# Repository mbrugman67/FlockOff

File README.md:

# FlockOff
This project started as a device specifically to detect Flock security ALPR devices, but has grown into a more generic WiFi/Bluetooth LE scanner/alert wardriving tool.

## Description
This started of strictly as a Flock detector, but grew into more.  In general, it is a device to monitor WiFi and BTLE networks, setting an indicator whenever a broadcaster is found that meets preset parameters.  For WiFi networks, those parameters can be a MAC OID or network name (SSID).  For Bluetooth, the matching criteria can be name, MAC, or by specific 16-bit UUIDs.

The hardware device consists of an ESP32-S3 dev board, a serial GPS module, and two LEDs for alerts and status.

There is a serial interface to the hardware device with a rich CLI (command-line interface).  The device can also be used stand-alone (results are stored to internal file system) or by scripting.

## Project structure
The files contained in the project:
+ `./hardware` - contains a KiCad project for the board
+ `./img` - images used in this README
+ `./py` - simply python3 script to interact with the flocker (notes below)
+ `./src` - source code (arduino project) for the ESP32 (notes below)
+ `./case` - sample 3D printer `.stl` and openSCAD files for a case

### Hardware

The hardware is dead simple - two dev modules, two through-hole 8mm WS2812 LEDs, and a small signal diode:
+ [ESP32-S3](https://www.amazon.com/Dual-core-Supported-Efficiency-Interface-Robotics/dp/B0DJ6NQFKX/ref=sxin_17_pa_sp_search_thematic_sspa?content-id=amzn1.sym.acab9f82-fc77-4a20-9021-7b5c22d80ec5%3Aamzn1.sym.acab9f82-fc77-4a20-9021-7b5c22d80ec5&crid=2JDD3FE6II334&cv_ct_cx=esp32s3&keywords=esp32s3&pd_rd_i=B0DJ6NQFKX&pd_rd_r=111273b0-33b8-492d-943f-a421e25d3cd0&pd_rd_w=tgPcF&pd_rd_wg=AKjP3&pf_rd_p=acab9f82-fc77-4a20-9021-7b5c22d80ec5&pf_rd_r=M8JMDJXXJ54DR9BMEQC6&qid=1765833241&s=electronics&sbo=RZvfv%2F%2FHxDF%2BO5021pAnSA%3D%3D&sprefix=esp32s3%2Celectronics%2C142&sr=1-2-6024b2a3-78e4-4fed-8fed-e1613be3bcce-spons&aref=L2fTwRUg09&sp_csd=d2lkZ2V0TmFtZT1zcF9zZWFyY2hfdGhlbWF0aWM&th=1) I picked this module because of small size, good price, and 8MB of both flash and PSRAM
+ [GPS Module](https://www.amazon.com/hiBCTR-Navigation-Positioning-Microcontroller-Sensitivity/dp/B0FL71WTQY/ref=sr_1_2?crid=2EM3EOXRCSTFT&dib=eyJ2IjoiMSJ9.XRWR-WnPLsz7cVN0GpjqJTxFRMO10MBskzPEVvz5LCTDXAtxa_rXf2wQrFndRzU50l7y__POWiiDMUXVK5OIa7VqEst8IqFH4xFvcnBHg-U0VY4qNZQPKFdzWL5Evdyj4AFWD0VpzcrnOxwnca7-Dr8wspdKucj2aYc0Gtoa1uRUl7K4ES9h20ztgmGDT3mPrt2tiQ-HN-FAgOPFQVPE3Pudl5vF2LNCPSp00W8Bhg5xvlYpIlCSGdX8GwmWiVH8u0OJW8YW5ridkpLchugFbq4H7w5SYdWBFkT73FZqAvk.YyvKMYAZdg815_BV_j8Fv4HH-0O0dOLUrndqKjRR0CQ&dib_tag=se&keywords=4+Pack+GPS+Module%2C+NEO-6M+Navigation+Positioning%2C+Arduino+GPS+for+Drone+Microcontroller%2C+High+Sensitivity+Receiver+with+Antenna%2C+Compatible+with+51+Microcontroller+STM32+Arduino+UNO+R3&nsdOptOutParam=true&qid=1765833097&s=electronics&sprefix=4+pack+gps+module%2C+neo-6m+navigation+positioning%2C+arduino+gps+for+drone+microcontroller%2C+high+sensitivity+receiver+with+antenna%2C+compatible+with+51+microcontroller+stm32+arduino+uno+r3%2Celectronics%2C158&sr=1-2) There is nothing special about this particular module; it is a basic GPS with NMEA serial interface, it was cheap, and in stock at Amazon
+ [WS1812 LEDs](https://www.adafruit.com/product/1734)  These are interesting in that they are the typical addressable LEDs, but in a through-hole 8mm package.  They are great for using as status indicators.  Also handy because there are so many libraries to work with them.
+ [1N4148 Diode](amazon.com/ALLECIN-1N4148-Schottky-Switching-Package/dp/B0CKRMK45V/ref=sr_1_6_sspa?dib=eyJ2IjoiMSJ9.5f18Rx_7lMSBN-40Nk5_scirzd5gVqG_sr48GsP-pxJ7RyARr5GHbm76WgpJle4ywCwcEGfv6m5ZR-PIBoBmRN28qtEe29DQYY84c263_q6oFDujaGGVK8-qabhrRd_IZtu2PwFHkKMBdiIw8IDQjSYkBxPm9DKi_AA6exCA7rmOiWGNdN9Oq0D-5c1H1XGK1kBii_ftCc-F3YiORaBovQ5vkFW9kAN3zzAu7IgDKEk.RF6rc4KmtAVvY9uUuLV-Zf6xt-HBLaOGQf1vvRW5V2U&dib_tag=se&keywords=1n4148&qid=1765833550&sr=8-6-spons&sp_csd=d2lkZ2V0TmFtZT1zcF9tdGY&psc=1) (Amazon link for reference, I had some in my parts bin).  This is used because it has a forward voltage drop of about .7V.

#### What's up with the diode?

Like pretty much all WS2812 LEDs, these need 5VDC to operate; 5VDC power, 5VDC data line.  The ESP32 is a 3.3 microcontroller, so what to do?

The USB connection supplies 5V which is regulated down to 3.3V for the microcontroller and associated stuff.  In the schematic above, `D3` is shown between the 5V USB power and the LED power in pin; that drops the voltage to about 4.3VDC.  That's just within spec for the LED, and it is still plenty bright.

The 3.3V signal data line from the ESP32 would be too low if the LED was powered by 5V, but is within spec for the LED when it is running at 4.3-ish volts.  It's a cheat to get away without having to use level converters; not something I'd do for a "real" production project, but good enough for here.

### Firmware
The firmware is written using the Arduino IDE.  In the past, I've always avoided that and used VS Code with my own Makefile or CMAKE, PlatformIO, or whatever.  I decided to go with Arduino in this case because I'm very unhappy with the integration of Copilot into VS Code (and really, the push to shove AI into everything).  For now, Ardiuno is just code.

For more specific information, see the `DEVELOPING.md` file.

### CLI Interface
There is a CLI available at the USB port at 115200/8N1.  The CLI uses ANSII escape codes for color, has tab-completion, up-arrow recall, and help:
```  
Flock Off $>help 
Use 'command -h' for detailed help on each command
        help - Print list of commands
        version - Display firmware version
        survey - Perform WiFi survey
        scan - Start continuous scan
        clear - Clear the console
        reset - Reboot the device
        ls - List files
        rm - Delete file
        write - Write test file
        mv - Rename file
        cp - Copy file
        cat - Cat file
        status - Get system status
        config - Get/Set config values
        criteria - Get/Set target matching criteria
```  
Passing a `-h` to any command will show help for that command, for example:
```  
Flock Off $>survey -h
survey [OPTION]
Perform a WiFi and/or Bluetooth survey.  Displays all results, not just those that match scan criteria.

  -i <INTERVAL>   interval in milliseconds to scan each WiFi channel
  -f <FILENAME>   save results to FILENAME in JSON format
  -n <NOTES>      add NOTES added for reference

If the -f parameter is not passed, JSON results will be displayed in the terminal.
```  
There is a flat filesystem included (flat, meaning no directories; all files are in a single directory). Basic Linux-type file management commands are available, but note that there is no 'globbing'; all filenames must be directly entered.  Examples:
```  
      371  01/22/26  18:25:46  autoscan.1.log
      163  01/22/26  18:42:01  autoscan.log
      208  12/31/69  18:02:32  config.json
    11300  01/22/26  18:26:04  system.1.log
    11107  01/22/26  18:25:30  system.2.log
    11347  01/22/26  18:43:37  system.log
Flock Off $>cat config.json
{"deviceName":"Super Secret Sniffer","timeZone":"CST6CDT,M3.2.0,M11.1.0","LEDBrightness":100,"debugEnabled":true,"debugLogRollCount":3,}
Flock Off $>
```  
Configuration is menu-driven:
```  
Flock Off $>config 
1) Set device name (Super Secret Sniffer)
2) Set timezone (CST6CDT,M3.2.0,M11.1.0)
3) Set max LED brightness (100)
4) Set debug logging (enabled)
5) Set scan logging (enabled)
6) Set debug file rolling count (3)
7) Set scan file rolling count (10)
8) Set minimum RSSI (-90)
9) Set minimum alert time (60)
Select number of item to change or 'x' to exit with no changes: 
```  
## LEDs
What do the LEDs do?
### GPS LED
| color | description |  
|---|---|  
| Green blink | GPS Fix good, communication good |  
| Purple blink | GPS no fix, communication good |  
| Red blink | No comms to GPS module |  

### RF LED
| color | description |  
|---|---|  
| Blue fade alert | Survey in progress | 
| Steady blue | Continuous scan in progress |  
| Alternating blue/purple | Continuous scan detecting target |  

## Continuous scans
The default action for the device is to continuously scan for targets in the area.  There are two ways to start a scan:
+ Power up the device, if no input is seen on the CLI in the first 5 seconds, continuous scanning will automatically begin
+ Using the `scan` command to start continuous scanning

### Stopping a scan
Press any key will connected to the serial port to stop the scan

### Scan logging and information
The RF LED will glow continuously blue when a scan is running.  If a target is seen, the LED will alternate blue/purple.  As targets are seen and "disappear" they will be listed in the serial terminal.  If enabled in configuration, the data will also be saved in rolling files in the filesystem - this allows "headless" operation with the ability to look at the results later.

Sample output in the serial terminal:
```  
Flock Off $>Starting scan - press any key to stop
ALERT! 01/23/26 01:03:13 42.8XXXX -87.9XXXX Matched MAC 14:6b:9c:e3:7f:3b (SHENZHEN BILIAN ELECTRONIC CO.，LTD)
```  

Sample scan log:  
```  
Flock Off $>ls 
      267  01/22/26  19:02:59  autoscan.1.log
      163  01/22/26  18:42:01  autoscan.2.log
      371  01/22/26  18:25:46  autoscan.3.log                                             
      267  01/22/26  19:04:01  autoscan.log                                               
      208  12/31/69  18:02:32  config.json                                                
     4557  01/22/26  18:50:13  survey.example.json                                        
    12384  01/22/26  19:03:01  system.1.log                                               
    11300  01/22/26  18:26:04  system.2.log
    11215  01/22/26  19:04:01  system.log
Flock Off $>cat autoscan.log
[00007907] 01/22/26 19:03:13 LOGGER::Started logger
[00007950] 01/22/26 19:03:13 WIFI::01/23/26 01:03:13 42.8XXXX -87.9XXXX; Matched mac 14:6b:9c:e3:7f:3b
[00055504] 01/22/26 19:04:01 SCAN::Ending scan, closing log.
[00055516] 01/22/26 19:04:01 LOG::Closing log!
```  

## Performing a site survey
A survey will report all WiFi and BTLE broadcasters in range.  Why perform a survey?  Maybe there's a known device that isn't triggering alerts, and we want to characterize it (find MAC address, if BT, see if there are any service UUIDs it's broadcasting).

Basic steps:
1) Connect to the device with a serial terminal of your choice (PuTTY on Windows, TIO/minicom on Linux, minicom on MAC).
2) Use the `status` command to be sure GPS has gotten a fix and that the data looks correct (GPS coordinates masked by me for privacy):
``` 
Flock Off $>status 
->Hardware:
        Chip model ESP32-S3
        Chip frequency 240 MHz
        Core count 2 cores
->GPS:
        GPS current coordinates are 42.8XXXX, -87.9XXXX
        GPS current time/date (gmt) is 00:47:52 1/23/2026
        Number of satellites currently tracked: 9
->Filesystem:
        Total capacity 4194304bytes, 53248 used (4044 KiB free)
->Memories:
        Internal total heap 324436 bytes, 88536 used (230 KiB free)
        PSRAM total heap 8388608 bytes, 58280 used (8192 KiB free)
->Wall clock:
        Current wall clock time is Thu, 22 Jan 2026 18:47:51 -0600
        Timezone is set to CST6CDT,M3.2.0,M11.1.0
```  
3) Use the `survey` command to start the survey.  Parameters are:
   + `-i INTERVAL` defines how much time (milliseconds) to spend on each WiFi channel
   + `-n NOTES` to save the results in a JSON file, with survey notes set to `NOTES`
   + `-f FILENAME` to save results
```  
Flock Off $>survey -i 2000 -n 'Example survey' -f survey.example.json
Survey starting
Survey done, found 16 WiFi devices, 13 Bluetooth devices.
Saving survey results to survey.example.json
Wrote 4557 bytes to file
```  
This example survey found 16 WiFi devices and 13 BTLE devices.  The data in the JSON file looks like this:  
```
Flock Off $>cat survey.example.json
{"SurveyNotes":"'Example survey","Device":"Super Secret Sniffer","LocationLongLat":[-87.9XXXX,42.8XXXX],"SatelliteCount":9,"DateTime":"2026-01-22 18:50:13","Timezone":"CST6CDT,M3.2.0,M11.1.0","DataVersion":2,"WiFiDevices":[{"Method":"WiFi","Type":"Data","Subtype":"ND (null no data)","SSID":"","SourceAddr":"4a:43:76:15:87:dd","DestAddr":"a0:36:bc:db:ca:a4","Channel":10,"RSSI":-20},{"Method":"WiFi","Type":"Management","Subtype":"beacon","SSID":"Open Wheel","SourceAddr":"08:36:c9:ed:b8:65","DestAddr":"ff:ff:ff:ff:ff:ff","Channel":4,"RSSI":-87},{"Method":"WiFi","Type":"Management","Subtype":"beacon","SSID":"NETGEAR05-Guest","SourceAddr":"c2:18:65:d2:d2:b2","DestAddr":"ff:ff:ff:ff:ff:ff","Channel":2,"RSSI":-87},{"Method":"WiFi","Type":"Data","Subtype":"Data","SSID":"","SourceAddr":"b2:28:aa:1c:0a:2a","DestAddr":"01:80:c2:00:00:00","Channel":1,"RSSI":-63},{"Method":"WiFi","Type":"Management","Subtype":"beacon","SSID":"flu","SourceAddr":"b2:28:aa:1c:0a:29","DestAddr":"ff:ff:ff:ff:ff:ff","Channel":1,"RSSI":-63},{"Method":"WiFi","Type":"Data","Subtype":"Data","SSID":"","SourceAddr":"a0:36:bc:db:ca:a0","DestAddr":"01:80:c2:00:00:00","Channel":6,"RSSI":-45},{"Method":"WiFi","Type":"Management","Subtype":"beacon","SSID":"virus","SourceAddr":"a0:36:bc:db:ca:a0","DestAddr":"ff:ff:ff:ff:ff:ff","Channel":6,"RSSI":-45},{"Method":"WiFi","Type":"Management","Subtype":"beacon","SSID":"flu_IoT","SourceAddr":"b2:28:aa:1c:0a:2a","DestAddr":"ff:ff:ff:ff:ff:ff","Channel":1,"RSSI":-64},{"Method":"WiFi","Type":"Data","Subtype":"QoS Data","SSID":"","SourceAddr":"b2:28:aa:1c:0a:29","DestAddr":"e0:75:26:a2:98:cc","Channel":1,"RSSI":-63},{"Method":"WiFi","Type":"Data","Subtype":"QoS Data","SSID":"","SourceAddr":"14:6b:9c:e3:7f:3b","DestAddr":"b2:28:aa:1c:0a:29","Channel":1,"RSSI":-54},{"Method":"WiFi","Type":"Data","Subtype":"QoS Data","SSID":"","SourceAddr":"cc:db:a7:93:ec:2c","DestAddr":"a0:36:bc:db:ca:a0","Channel":7,"RSSI":-71},{"Method":"WiFi","Type":"Management","Subtype":"beacon","SSID":"<HIDDEN>","SourceAddr":"cc:28:aa:1c:0a:28","DestAddr":"ff:ff:ff:ff:ff:ff","Channel":1,"RSSI":-63},{"Method":"WiFi","Type":"Data","Subtype":"Data","SSID":"","SourceAddr":"a0:8a:06:6f:ec:fa","DestAddr":"01:00:5e:00:00:07","Channel":6,"RSSI":-84},{"Method":"WiFi","Type":"Data","Subtype":"Data","SSID":"","SourceAddr":"cc:28:aa:1c:0a:28","DestAddr":"01:80:c2:00:00:00","Channel":1,"RSSI":-64},{"Method":"WiFi","Type":"Data","Subtype":"ND (null no data)","SSID":"","SourceAddr":"e0:75:26:a2:98:cc","DestAddr":"b2:28:aa:1c:0a:29","Channel":1,"RSSI":-76},{"Method":"WiFi","Type":"Management","Subtype":"beacon","SSID":"NETGEAR05","SourceAddr":"94:18:65:d2:d2:b1","DestAddr":"ff:ff:ff:ff:ff:ff","Channel":2,"RSSI":-90}],"BLEDevices":[{"Method":"BTLE","Name":"N00DM","MAC":"c7:06:90:c0:c4:6c","RSSI":-84,"UUID16bit":[65199],"UUID128bit":[],"DataUUID16bit":[65199],"DataUUID128bit":[]},{"Method":"BTLE","Name":"OfficeJet 5200 series","MAC":"86:a9:3e:bc:5c:c9","RSSI":-86,"UUID16bit":[65144],"UUID128bit":[],"DataUUID16bit":[],"DataUUID128bit":[]},{"Method":"BTLE","Name":"","MAC":"47:d1:13:3a:79:de","RSSI":-70,"UUID16bit":[],"UUID128bit":[],"DataUUID16bit":[],"DataUUID128bit":[]},{"Method":"BTLE","Name":"","MAC":"6b:7a:e6:9b:f5:d2","RSSI":-65,"UUID16bit":[],"UUID128bit":[],"DataUUID16bit":[],"DataUUID128bit":[]},{"Method":"BTLE","Name":"","MAC":"66:95:29:56:70:e9","RSSI":-69,"UUID16bit":[],"UUID128bit":[],"DataUUID16bit":[],"DataUUID128bit":[]},{"Method":"BTLE","Name":"","MAC":"d4:0a:5d:22:d4:e9","RSSI":-61,"UUID16bit":[],"UUID128bit":[],"DataUUID16bit":[],"DataUUID128bit":[]},{"Method":"BTLE","Name":"","MAC":"63:13:27:3d:4d:22","RSSI":-62,"UUID16bit":[],"UUID128bit":[],"DataUUID16bit":[],"DataUUID128bit":[]},{"Method":"BTLE","Name":"","MAC":"1d:2a:e8:54:5e:f4","RSSI":-69,"UUID16bit":[],"UUID128bit":[],"DataUUID16bit":[65267],"DataUUID128bit":[]},{"Method":"BTLE","Name":"","MAC":"a8:51:ab:c6:11:25","RSSI":-75,"UUID16bit":[],"UUID128bit":[],"DataUUID16bit":[],"DataUUID128bit":[]},{"Method":"BTLE","Name":"","MAC":"3c:5c:ae:fd:ff:0d","RSSI":-53,"UUID16bit":[],"UUID128bit":[],"DataUUID16bit":[64753],"DataUUID128bit":[]},{"Method":"BTLE","Name":"","MAC":"79:d2:f7:d7:5d:22","RSSI":-75,"UUID16bit":[],"UUID128bit":[],"DataUUID16bit":[],"DataUUID128bit":[]},{"Method":"BTLE","Name":"","MAC":"32:2b:12:15:81:9a","RSSI":-51,"UUID16bit":[],"UUID128bit":[],"DataUUID16bit":[64753],"DataUUID128bit":[]},{"Method":"BTLE","Name":"[TV] Samsung 8 Series (65)","MAC":"8c:ea:48:a7:2c:03","RSSI":-72,"UUID16bit":[],"UUID128bit":[],"DataUUID16bit":[],"DataUUID128bit":[]}]}
```  
### Interpreting survey results
The included python scripts can pull the survey data from the device and populate some database tables (sqlite3) for analysis.

To do this, start by going to the `./py` directory and running the script.  There are some Python modules needed; they can be installed with the included requirements file (`pip3 install -r requirements.txt`)

*Note - it is always recommended to use a virtual environment with python scripts that require different modules.  See python documentation on how to create and use a virtual environment if necessary.*

Start by listing the files on the device (make sure you are no longer connected to it by serial terminal):
```  
┌──(venv)─(matty💊s76)-[~/data/projects/FlockOff/py]
└─$ python3 ./flock.py --dbfile example.db --port /dev/ttyACM0 --dir                
config.bak
config.json
survey.00.json
survey.01.json
survey.example.json
system.log
```  
The parameters to the `flock.py` script are:
+ `--port PORT` - the serial port of the connected device
+ `--dbfile FILE` - name of the database file to use (it will be created if it does not exist).  This is only required if the `load` command is issued.
+ Command - this is one of a few commands:
  + `--dir` - list the files on the device
  + `--cat FILE` - list the contents of the specified file
  + `--load FILE` - load the specified JSON file into database tables'
  + `--download FILE` - download the specified FILE from the device to the local filesystem.  The local copy will have the same name as the file on the device.

The above `--dir` command showed our `survey.example.json` from the survey.  Let's load it into the database tables:
```  
┌──(venv)─(matty💊s76)-[~/data/projects/FlockOff/py]
└─$ python3 ./flock.py --dbfile example.db --port /dev/ttyACM0 --load survey.example.json
Loaded 12 WiFi devices, 21 BTLE devices from survey "'Example" at 2025-12-15 15:56:52
```  

Note that if the database file didn't exist before this command, the script will also populate the data tables with the YAML and JSON files for known manufacturer OID and UUID data.

### Survey database

The database schema can be seen in `./src/py/survey.db.schema`

The sqlite3 database can be explored with a gui tool or the command line.  The `surveys` table shows basic information about the a survey json file (using `sqlite3` command line tool):
```  
sqlite> .mode box
sqlite> .headers on
sqlite> select * from surveys;
┌───────────┬──────────┬─────────────────────┬───────────┬───────────┬──────────┐
│ surveyInx │  notes   │      dateTime       │ longitude │ lattitude │ satCount │
├───────────┼──────────┼─────────────────────┼───────────┼───────────┼──────────┤
│ 1         │ 'Example │ 2025-12-15 15:56:52 │ 42.0001   │ -87.0001  │ 8        │
└───────────┴──────────┴─────────────────────┴───────────┴───────────┴──────────┘
```  
 The `surveyInx` field is a foreign key into the `wifi_data`, `wifi_management` and `btle` tables.  This allows multiple surveys to be loaded into a single database file

`notes` is the value from the `-j NOTES` parameter of the `survey` command.  `dateTime`, `longitude`, `lattitude`, and `satCount` are populated by the GPS module.

`wifi_data` contains all captured WiFi Data packets; `wifi_management` contains all captured WiFi Management packets (think access point beacons, probe responses, etc.).  They can be joined to find all devices and the access points to which they are connected:   
```
select distinct sta.subtype "station data subtype",
		ap.ssid "AP SSID", 
		ap.bssid "AP BSSID", 
		sta.sourceAddr "station MAC", 
		sta.channel "CH",
		mv.vendorName "station vendor" 
from wifi_data sta
join wifi_management ap on ap.bssid = sta.destAddr and ap.channel = sta.channel and ap.surveyInx = sta.surveyInx
left join mac_vendor mv on mv.prefix like substr(sta.sourceAddr, 1, 8) 
where sta.surveyInx = 2
order by ap.bssid;

┌──────────────────────┬────────────────────┬───────────────────┬───────────────────┬────┬────────────────────────────────────────┐
│ station data subtype │      AP SSID       │     AP BSSID      │    station MAC    │ CH │             station vendor             │
├──────────────────────┼────────────────────┼───────────────────┼───────────────────┼────┼────────────────────────────────────────┤
│ ND (null no data)    │ virus              │ a0:36:bc:db:ca:a0 │ cc:db:a7:93:ec:2c │ 6  │ Espressif Inc.                         │
│ QoS Data             │ virus              │ a0:36:bc:db:ca:a0 │ cc:db:a7:93:ec:2c │ 6  │ Espressif Inc.                         │
│ ND (null no data)    │ SpectrumSetup-ECFD │ a0:8a:06:6f:ec:fa │ bc:35:1e:77:8a:9f │ 6  │ Tuya Smart Inc.                        │
│ ND (null no data)    │ SpectrumSetup-ECFD │ a0:8a:06:6f:ec:fa │ 30:fc:eb:84:38:ce │ 7  │ LG Electronics (Mobile Communications) │
│ ND (null no data)    │ SpectrumSetup-ECFD │ a0:8a:06:6f:ec:fa │ 30:fc:eb:84:38:ce │ 6  │ LG Electronics (Mobile Communications) │
│ QoS Data             │ flu                │ b2:28:aa:1c:0a:29 │ e0:75:26:a2:98:cc │ 1  │ China Dragon Technology Limited        │
│ ND QoS               │ flu                │ b2:28:aa:1c:0a:29 │ 14:6b:9c:e3:7f:3b │ 2  │ SHENZHEN BILIAN ELECTRONIC CO.，LTD    │
│ QoS Data             │ flu                │ b2:28:aa:1c:0a:29 │ 14:6b:9c:e3:7f:3b │ 1  │ SHENZHEN BILIAN ELECTRONIC CO.，LTD    │
│ QoS Data             │ flu                │ b2:28:aa:1c:0a:29 │ 18:b4:30:a0:24:fa │ 1  │ Nest Labs Inc.                         │
└──────────────────────┴────────────────────┴───────────────────┴───────────────────┴────┴────────────────────────────────────────┘
```

The `btle` table contains bluetooth broadcasters:
```  
sqlite> select b.name, b.mac, b.rssi from btle as b join surveys s on b.surveyInx = s.surveyInx order by b.mac;
┌───────────────────────┬───────────────────┬──────┐
│         name          │        mac        │ rssi │
├───────────────────────┼───────────────────┼──────┤
│                       │ 01:c5:61:6d:2c:b4 │ -53  │
│                       │ 04:a0:29:10:68:e4 │ -78  │
│                       │ 08:66:98:f2:a3:ba │ -84  │
│                       │ 34:fe:3e:a1:f5:e2 │ -63  │
│                       │ 56:f6:b3:ad:60:5f │ -82  │
│                       │ 66:7f:66:1d:ec:ce │ -68  │
│                       │ 6d:67:db:fd:9e:67 │ -84  │
│                       │ 6e:d3:64:c3:af:77 │ -79  │
│                       │ 77:50:8c:84:fa:72 │ -45  │
│                       │ 78:90:0b:c0:26:1b │ -69  │
│                       │ 7e:91:43:7c:ff:bf │ -75  │
│ OfficeJet 5200 series │ 86:a9:3e:bc:5c:c9 │ -76  │
│                       │ 8c:ea:48:a7:2c:03 │ -73  │
│                       │ a8:51:ab:c6:11:25 │ -82  │
│                       │ c0:c9:9b:f2:d7:43 │ -75  │
│                       │ c1:cf:e2:c9:64:5f │ -85  │
│                       │ ca:ba:59:12:f6:0d │ -66  │
│ N00DM                 │ ce:a3:ad:95:04:29 │ -80  │
│                       │ d5:93:9d:03:9f:f5 │ -80  │
│                       │ ea:a8:d0:6f:67:89 │ -84  │
│                       │ ec:9d:4d:3c:28:2b │ -68  │
└───────────────────────┴───────────────────┴──────┘
```  
There are quite a few BTLE devices found.  To narrow it down to those that are broadcasting a UUID:
```  
sqlite> select b.name, b.mac, u.uuid16 from btle b join uuid16 u on b.btInx = u.btInx where b.surveyInx = 1 order by b.mac;
┌───────────────────────┬───────────────────┬────────┐
│         name          │        mac        │ uuid16 │
├───────────────────────┼───────────────────┼────────┤
│ OfficeJet 5200 series │ 86:a9:3e:bc:5c:c9 │ 65144  │
│ N00DM                 │ ce:a3:ad:95:04:29 │ 65199  │
└───────────────────────┴───────────────────┴────────┘
```

**More SQL examples can be found in `./example.sql`**

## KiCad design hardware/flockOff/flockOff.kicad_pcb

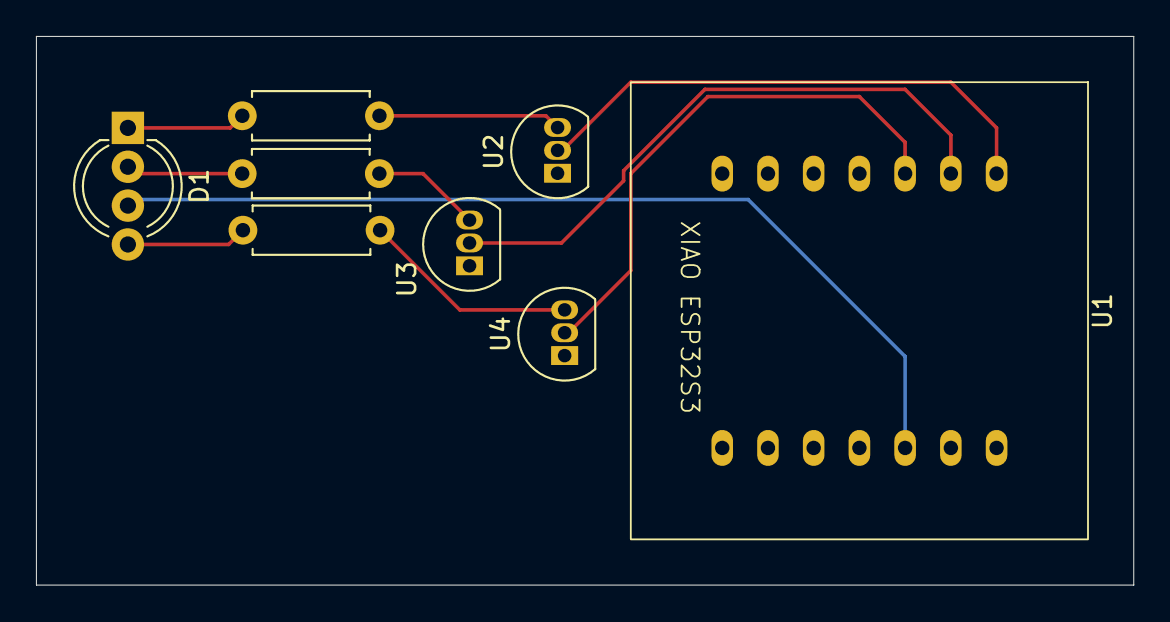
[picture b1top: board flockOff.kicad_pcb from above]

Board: 2 copper layers, 61.0 x 30.5 mm, 8 parts (0 on the bottom side), 11 nets.

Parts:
D1: GPS_LED; LED_D5.0mm-4_RGB_Wide_Pins
R1: 47 Ohm; R_Axial_DIN0207_L6.3mm_D2.5mm_P7.62mm_Horizontal
R2, R3: 10 Ohm; R_Axial_DIN0207_L6.3mm_D2.5mm_P7.62mm_Horizontal
U1: XIAO_ESP32S3
U2, U3, U4: TO-92L_Inline

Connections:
+3.3V: D1.3 (A), U1.12 (3v3)
/COMM_LED_B: U1.3 (GPIO3), U4.2 (G)
/COMM_LED_G: U1.2 (GPIO2), U3.2 (G)
/COMM_LED_R: U1.1 (GPIO1), U2.2 (G)
GND: U1.13 (GND), U2.1 (S), U3.1 (S), U4.1 (S)
unnamed: D1.1 (BK), R1.2
unnamed: D1.2 (GK), R2.2
unnamed: D1.4 (RK), R3.2
unnamed: R1.1, U2.3 (D)
unnamed: R2.1, U3.3 (D)
unnamed: R3.1, U4.3 (D)

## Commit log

2025-10-20 Add construction status to README
    Added a note indicating that the project is under construction.
    Also, Copilot is shit. Not as in "The Shit!" meaning good; as in "This is a piece of shit", meaning it's bad.
2025-10-23 Initial arduino code push. GPS, LEDs first draft done. Dummy code in main
2025-10-29 enough for now, working on board
2025-11-01 starting on some proto hardware, learning KiCad
2025-11-01 trying addressable leds
2026-01-09 Adding lanyard ring to case, re-rendering .stl files
2026-01-09 new docs
2026-01-10 added 1mm to top to better handle counterbore of 3mm SHCS
2026-01-10 some docs
2026-01-10 ope, forgot to MarkDown like an image
2026-01-10 documenting
2026-01-11 Fixed bt scan memory leak
2026-01-12 cleaning up some cruft
2026-01-13 fix allocation/free, docs docs docs
2026-01-13 Missed a file in docs
2026-01-14 Adding general data WiFI packets
2026-01-14 Adding WiFi data packet gathering, major (breaking) database and python changes
2026-01-14 Add more wifi packets (#13)
    * Adding general data WiFI packets
    * Adding WiFi data packet gathering, major (breaking) database and python changes
2026-01-15 Added 'version' command, changed database schema to add device name to surveys table, updated scanner to tweak BT duration. Changes to example sql and python script to go with DB schema changes.
2026-01-17 Larger survey json buffer due to more wifi devices, changes to CONTRIBUTING.md DEVELOPING.md LICENSE README.md TODO.md assembly.md case example.sql hardware img py src command to show file last modif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
2026-01-19 starting framework for scan command, added config values, adding scan update method
2026-01-19 continuous scan and autoscan in place; needs filtering
2026-01-20 beginning to add match criteria handler
2026-01-21 Added new Allocator class for STL types to go into PS_RAM instead of SRAM, added python script to get OUIs from json, add matching stuff
2026-01-21 Missed this file in last PR
2026-01-21 updated header image, copyright date; corrected reversed lat/long
2026-01-23 cleaning up flk namespace, updates to README
2026-02-03 clean up logging and messaging around wifi matching, added default wifi ssid matching
2026-02-10 Adding UUID32 size BT data and service
2026-02-11 Updating sample SQL queries and fixing bug with python
